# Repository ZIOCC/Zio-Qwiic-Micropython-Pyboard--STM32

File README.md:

# Zio-Qwiic-Micropython-Pyboard--STM32

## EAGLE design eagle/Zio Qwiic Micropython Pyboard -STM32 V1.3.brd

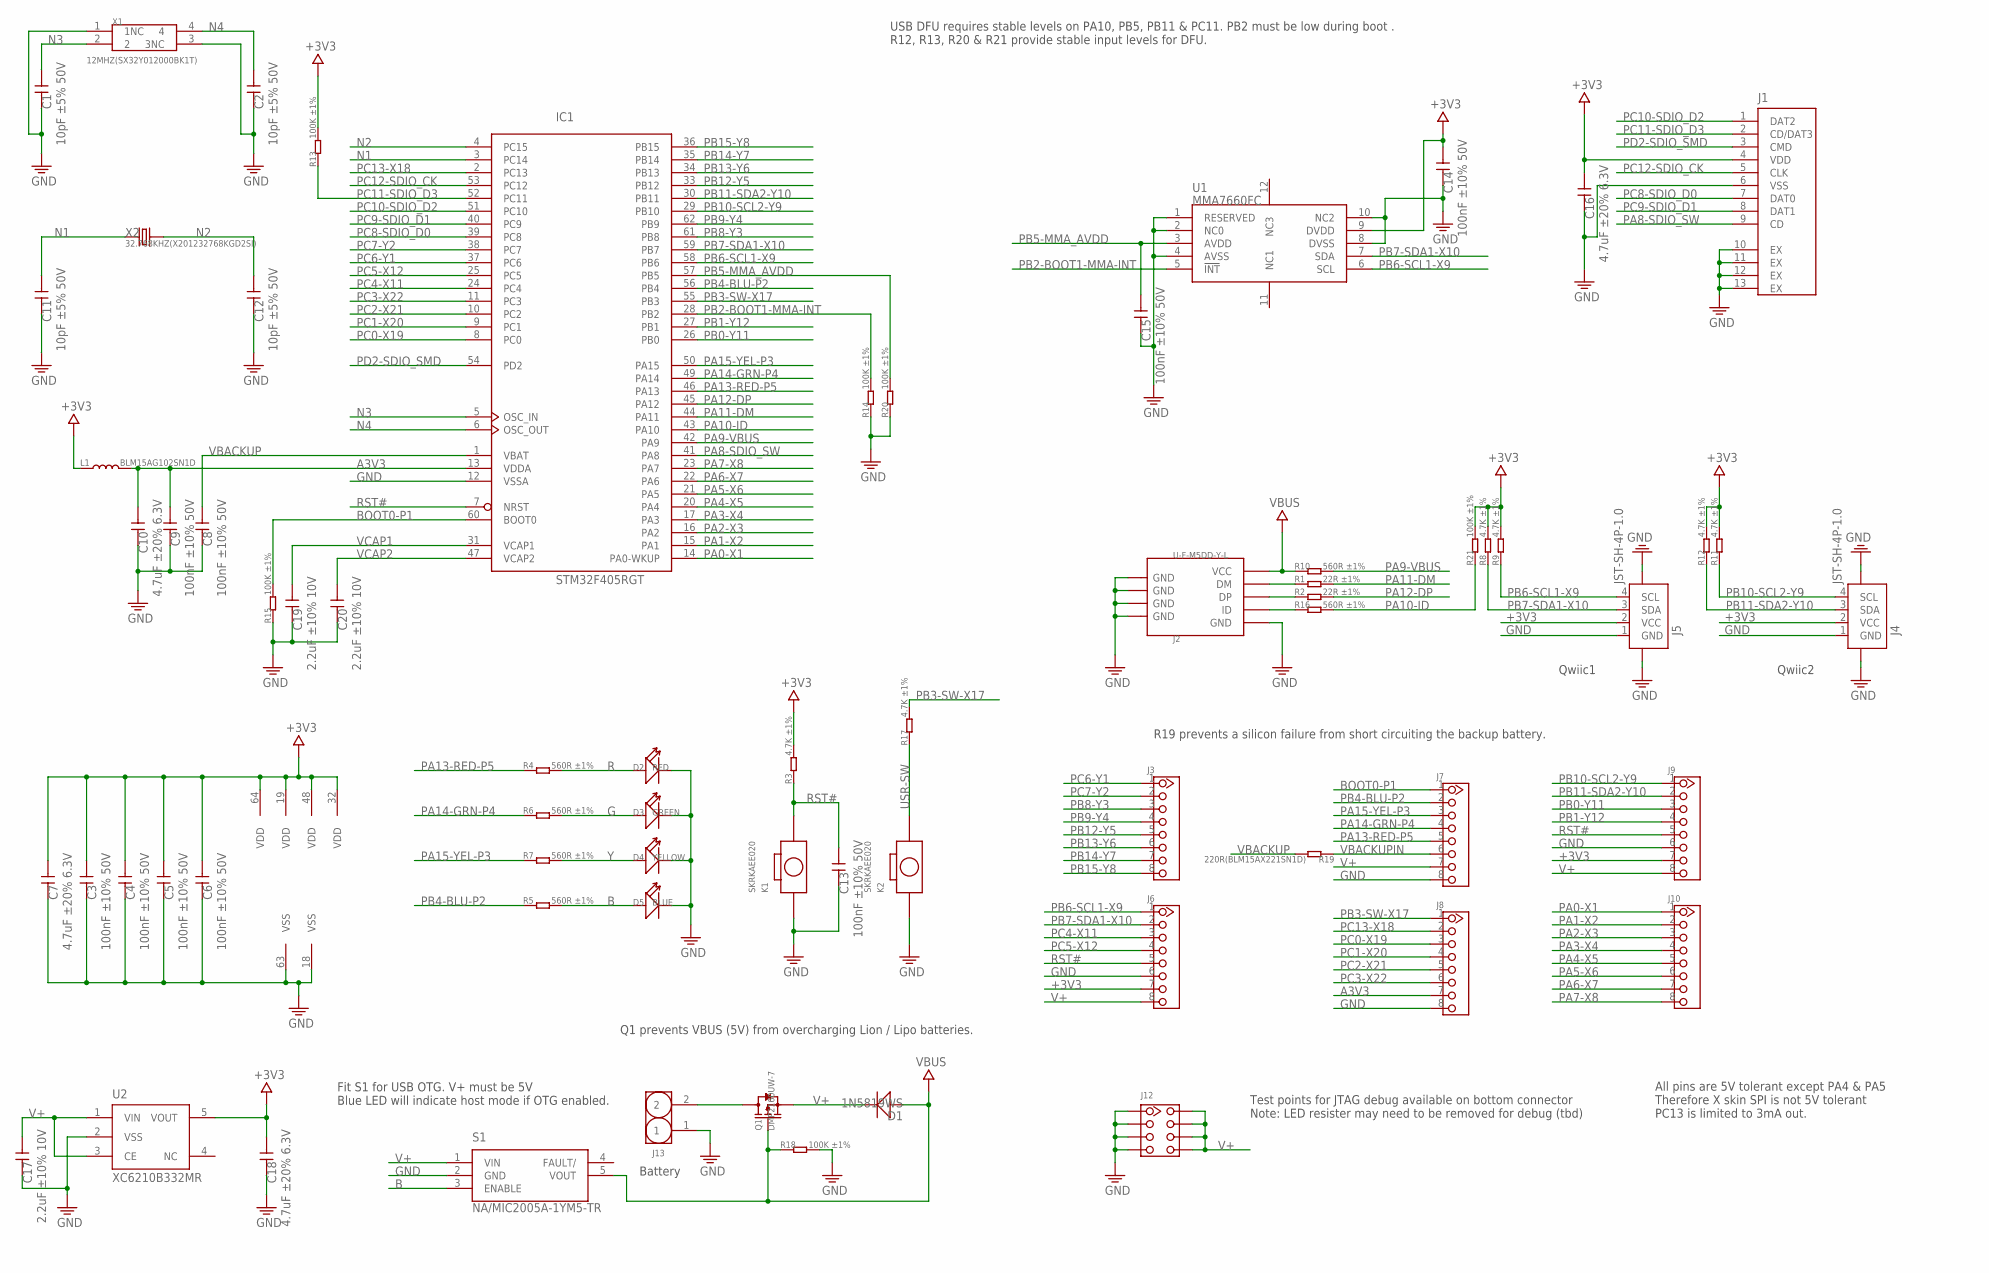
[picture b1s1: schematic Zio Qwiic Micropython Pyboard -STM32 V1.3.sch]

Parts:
C1, C2, C11, C12: 10pF ±5% 50V; C0402
C3, C4, C5, C6, C8, C9, C13, C14, C15: 100nF ±10% 50V; C0402
C7, C10, C16, C18: 4.7uF ±20% 6.3V; C0402
C17, C19, C20: 2.2uF ±10% 10V; C0402
D1: 1N5819WS; SOD323
D2: RED; LED-0603
D3: GREEN; LED-0603
D4: YELLOW; LED-0603
D5: BLUE; LED-0603
IC1: STM32F405RGT; LQFP64
J1: TF_CARD
J2: U-F-M5DD-Y-L; MICRO-SMD
J3, J6, J7, J8, J9, J10: HEADER-8P-NS; 8P-2.54-60/35MIL-NS
J4, J5: JST-SH-4P-1.0; JST-SH-4P
J12: HEADER-2X4P-NS; 2X4P-2.54-NS
J13: HEADER-2P-2.0-90; PH2.0-2P-90
K1, K2: SKRKAEE020
L1: BLM15AG102SN1D; L0402
Q1: DMP2160UW-7; SOT-323
R1, R2: 22R ±1%; R0402
R3, R8, R9, R11, R12, R17: 4.7K ±1%; R0402
R4, R5, R6, R7, R10, R16: 560R ±1%; R0402
R13, R14, R15, R18, R20, R21: 100K ±1%; R0402
R19: 220R(BLM15AX221SN1D); R0402
S1: NA/MIC2005A-1YM5-TR; SOT95P280X130-5N
U1: MMA7660FC; DFN10
U2: XC6210B332MR; SOT23-5
X1: 12MHZ(SX32Y012000BK1T); 4P-SMD-3.2X2.5
X2: 32.768KHZ(X201232768KGD2SI); 2.0X12MM

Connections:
+3V3: C3.2, C4.2, C5.2, C6.2, C7.2, C14.2, C16.2, C18.2, IC1.19 (VDD), IC1.32 (VDD), IC1.48 (VDD), IC1.64 (VDD), J1.4 (VDD), J4.2 (VCC), J5.2 (VCC), J6.7, J9.7, L1.1, R3.2, R8.2, R9.2, R11.2, R12.2, R13.2, R21.2, U1.9 (DVDD), U2.5 (VOUT)
A3V3: C9.2, C10.2, IC1.13 (VDDA), J8.7, L1.2
B: D5.+, R5.2, S1.3 (ENABLE)
BOOT0-P1: IC1.60 (BOOT0), J7.1, R15.2
G: D3.+, R6.2
GND: C1.1, C2.1, C3.1, C4.1, C5.1, C6.1, C7.1, C8.1, C9.1, C10.1, C11.1, C12.1, C13.1, C14.1, C15.1, C16.1, C17.1, C18.1, C19.1, C20.1, D2.-, D3.-, D4.-, D5.-, IC1.12 (VSSA), IC1.18 (VSS), IC1.63 (VSS), J1.6 (VSS), J1.10 (EX), J1.11 (EX), J1.12 (EX), J1.13 (EX), J2.GND, J2.S1 (GND), J2.S1@1 (GND), J2.S1@2 (GND), J2.S2 (GND), J2.S2@1 (GND), J2.S2@2 (GND), J2.S3 (GND), J2.S3@1 (GND), J2.S3@2 (GND), J2.S4 (GND), J2.S4@1 (GND), J2.S4@2 (GND), J2.S5 (GND), J2.S6 (GND), J4.1 (GND), J4.NC1 (5), J4.NC2 (6), J5.1 (GND), J5.NC1 (5), J5.NC2 (6), J6.6, J7.8, J8.8, J9.6, J12.1, J12.2, J12.3, J12.4, J13.1, K1.1, K2.1, R14.1, R15.1, R18.2, R20.1, S1.2 (GND), U1.1 (RESERVED), U1.2 (NC0), U1.4 (AVSS), U1.8 (DVSS), U1.10 (NC2), U2.2 (VSS), X1.1 (1NC), X1.3 (3NC)
N1: C11.2, IC1.3 (PC14), X2.1
N2: C12.2, IC1.4 (PC15), X2.2
N3: C1.2, IC1.5 (OSC_IN), X1.2
N4: C2.2, IC1.6 (OSC_OUT), X1.4
unnamed: J2.D- (DM), R1.1
unnamed: J2.D+ (DP), R2.1
unnamed: J2.ID, R16.1
unnamed: J13.2, Q1.3 (D)
PA0-X1: IC1.14 (PA0-WKUP), J10.1
PA1-X2: IC1.15 (PA1), J10.2
PA2-X3: IC1.16 (PA2), J10.3
PA3-X4: IC1.17 (PA3), J10.4
PA4-X5: IC1.20 (PA4), J10.5
PA5-X6: IC1.21 (PA5), J10.6
PA6-X7: IC1.22 (PA6), J10.7
PA7-X8: IC1.23 (PA7), J10.8
PA8-SDIO_SW: IC1.41 (PA8), J1.9 (CD)
PA9-VBUS: IC1.42 (PA9), R10.2
PA10-ID: IC1.43 (PA10), R16.2, R21.1
PA11-DM: IC1.44 (PA11), R1.2
PA12-DP: IC1.45 (PA12), R2.2
PA13-RED-P5: IC1.46 (PA13), J7.5, R4.1
PA14-GRN-P4: IC1.49 (PA14), J7.4, R6.1
PA15-YEL-P3: IC1.50 (PA15), J7.3, R7.1
PB0-Y11: IC1.26 (PB0), J9.3
PB1-Y12: IC1.27 (PB1), J9.4
PB2-BOOT1-MMA-INT: IC1.28 (PB2), R14.2, U1.5 (!INT)
PB3-SW-X17: IC1.55 (PB3), J8.1, R17.2
PB4-BLU-P2: IC1.56 (PB4), J7.2, R5.1
PB5-MMA_AVDD: C15.2, IC1.57 (PB5), R20.2, U1.3 (AVDD)
PB6-SCL1-X9: IC1.58 (PB6), J5.4 (SCL), J6.1, R9.1, U1.6 (SCL)
PB7-SDA1-X10: IC1.59 (PB7), J5.3 (SDA), J6.2, R8.1, U1.7 (SDA)
PB8-Y3: IC1.61 (PB8), J3.3
PB9-Y4: IC1.62 (PB9), J3.4
PB10-SCL2-Y9: IC1.29 (PB10), J4.4 (SCL), J9.1, R11.1
PB11-SDA2-Y10: IC1.30 (PB11), J4.3 (SDA), J9.2, R12.1
PB12-Y5: IC1.33 (PB12), J3.5
PB13-Y6: IC1.34 (PB13), J3.6
PB14-Y7: IC1.35 (PB14), J3.7
PB15-Y8: IC1.36 (PB15), J3.8
PC0-X19: IC1.8 (PC0), J8.3
PC1-X20: IC1.9 (PC1), J8.4
PC2-X21: IC1.10 (PC2), J8.5
PC3-X22: IC1.11 (PC3), J8.6
PC4-X11: IC1.24 (PC4), J6.3
PC5-X12: IC1.25 (PC5), J6.4
PC6-Y1: IC1.37 (PC6), J3.1
PC7-Y2: IC1.38 (PC7), J3.2
PC8-SDIO_D0: IC1.39 (PC8), J1.7 (DAT0)
PC9-SDIO_D1: IC1.40 (PC9), J1.8 (DAT1)
PC10-SDIO_D2: IC1.51 (PC10), J1.1 (DAT2)
PC11-SDIO_D3: IC1.52 (PC11), J1.2 (CD/DAT3), R13.1
PC12-SDIO_CK: IC1.53 (PC12), J1.5 (CLK)
PC13-X18: IC1.2 (PC13), J8.2
PD2-SDIO_SMD: IC1.54 (PD2), J1.3 (CMD)
R: D2.+, R4.2
RST#: C13.2, IC1.7 (NRST), J6.5, J9.5, K1.2, R3.1
USR-SW: K2.2, R17.1
V+: C17.2, D1.-, J6.8, J7.7, J9.8, J12.5, J12.6, J12.7, J12.8, Q1.2 (S), S1.1 (VIN), U2.1 (VIN), U2.3 (CE)
VBACKUP: C8.2, IC1.1 (VBAT), R19.2
VBACKUPIN: J7.6, R19.1
VBUS: D1.+, J2.VBUS (VCC), Q1.1 (G), R10.1, R18.1, S1.5 (VOUT)
VCAP1: C19.2, IC1.31 (VCAP1)
VCAP2: C20.2, IC1.47 (VCAP2)
Y: D4.+, R7.2

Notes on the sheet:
Qwiic1
Qwiic2
Battery
USB DFU requires stable levels on PA10, PB5, PB11 & PC11. PB2 must be low during boot . R12, R13, R20 & R21 provide stable input levels for DFU.
Q1 prevents VBUS (5V) from overcharging Lion / Lipo batteries.
Fit S1 for USB OTG. V+ must be 5V Blue LED will indicate host mode if OTG enabled.
Test points for JTAG debug available on bottom connector Note: LED resister may need to be removed for debug (tbd)
R19 prevents a silicon failure from short circuiting the backup battery.
All pins are 5V tolerant except PA4 & PA5 Therefore X skin SPI is not 5V tolerant PC13 is limited to 3mA out.

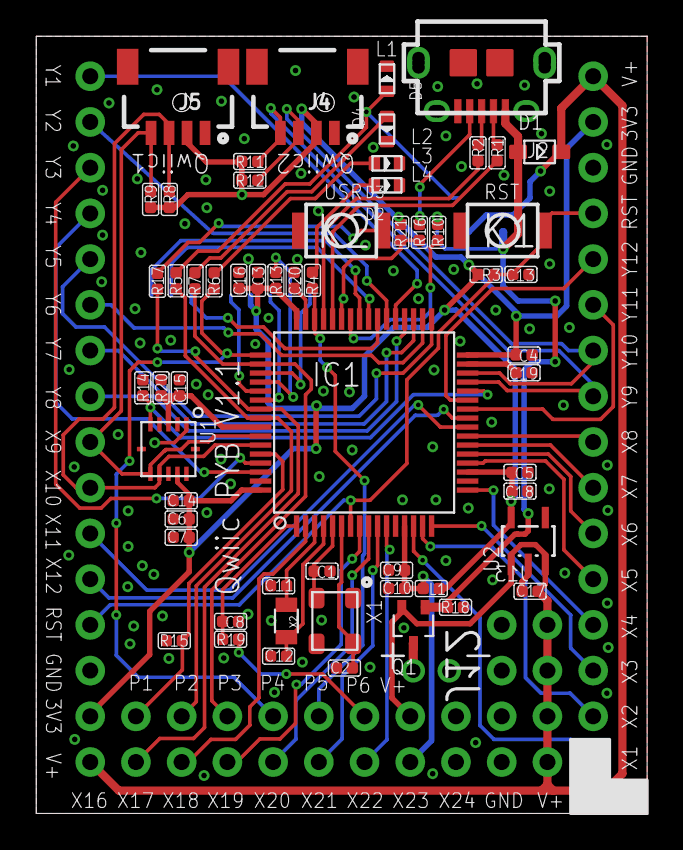
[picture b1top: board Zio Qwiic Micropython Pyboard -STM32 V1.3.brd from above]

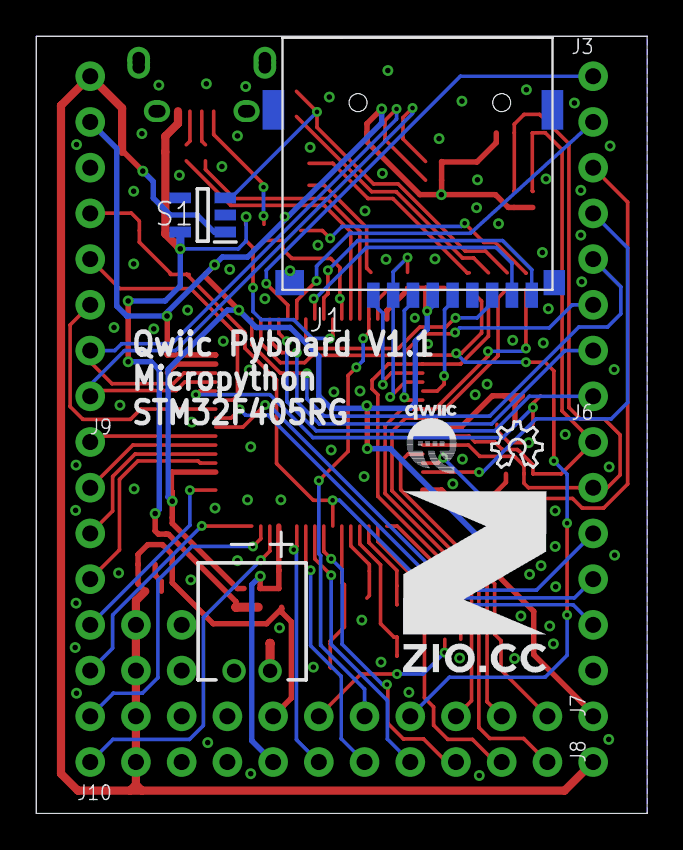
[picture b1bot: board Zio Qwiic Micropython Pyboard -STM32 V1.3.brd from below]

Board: 2 copper layers, 33.9 x 43.2 mm, 71 parts (13 on the bottom side), 71 nets.

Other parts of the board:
U$12: 10MM
U$13: QWIIC-LOGO-SMALL
U$14: OSHW_6X100_NOTEXT

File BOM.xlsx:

| BOM/PCBA quantity:
 | Project Name:
# | Part ID/Reference | Manufacturer | Part Number | Description | Value | Package | THT | Pins/Pads Qty | Source/Link/Datasheet/Note | Quantity/per BOM | NOTE
1 | C1, C2, C11, C12 |  |  |  | 10pF ±5% 50V | C0402 |  |  |  | 4
2 | C3, C4, C5, C6, C8, C9, C13, C14, C15 |  |  |  | 100nF ±10% 50V | C0402 |  |  |  | 9
3 | C7, C10, C16, C18 |  |  |  | 4.7uF ±20% 6.3V | C0402 |  |  |  | 4
4 | C17, C19, C20 |  |  |  | 2.2uF ±10% 10V | C0402 |  |  |  | 3
5 | D1 |  | 1N5819WS |  | 1N5819WS | SOD323 |  |  |  | 1
6 | D2 |  |  |  | RED | LED-0603 |  |  |  | 1
7 | D3 |  |  |  | GREEN | LED-0603 |  |  |  | 1
8 | D4 |  |  |  | YELLOW | LED-0603 |  |  |  | 1
9 | D5 |  |  |  | BLUE | LED-0603 |  |  |  | 1
10 | IC1 |  | STM32F405RGT |  | STM32F405RGT | LQFP64 |  |  |  | 1
11 | J1 |  | 带自弹TF卡座 |  | TF_CARD | TF_CARD |  |  |  | 1
12 | J2 |  | U-F-M5DD-Y-L |  | U-F-M5DD-Y-L | MICRO-SMD |  |  |  | 1
13 | J3, J6, J7, J8, J9, J10 |  | NA |  | NA | 8P-2.54-60/35MIL-NS |  |  |  | 6
14 | J4, J5 |  |  |  | JST-SH-4P-1.0 | JST-SH-4P |  |  |  | 2
15 | J12 |  | NA |  | NA | 2X4P-2.54-NS |  |  |  | 1
16 | J13 |  | NA |  | NA | PH2.0-2P-90 |  |  |  | 1
17 | K1, K2 |  | SKRKAEE020 |  | SKRKAEE020 | SKRKAEE020 |  |  |  | 2
18 | L1 |  | BLM15AG102SN1D |  | BLM15AG102SN1D | L0402 |  |  |  | 1
19 | Q1 |  | DMP2160UW-7 |  | DMP2160UW-7 | SOT-323 |  |  |  | 1
20 | R1, R2 |  |  |  | 22R ±1% | R0402 |  |  |  | 2
21 | R3, R8, R9, R11, R12, R17 |  |  |  | 4.7K ±1% | R0402 |  |  |  | 6
22 | R4, R5, R6, R7, R10, R16 |  |  |  | 560R ±1% | R0402 |  |  |  | 6
23 | R13, R14, R15, R18, R20, R21 |  |  |  | 100K ±1% | R0402 |  |  |  | 6
24 | R19 |  | BLM15AX221SN1D |  | 220R ±1% | R0402 |  |  |  | 1
25 | S1 |  | NA |  | NA/MIC2005A-1YM5-TR | SOT95P280X130-5N |  |  |  | 1
26 | U1 |  | MMA7660FC |  | MMA7660FC | DFN10 |  |  |  | 1
27 | U2 |  | XC6210B332MR |  | XC6210B332MR | SOT23-5 |  |  |  | 1
28 | X1 |  | SX32Y012000BK1T |  | 12MHZ(SX32Y012000BK1T) | 4P-SMD-3.2X2.5 |  |  |  | 1
29 | X2 |  | X201232768KGD2SI |  | 32.768KHZ(X201232768KGD2SI) | 2.0X12MM |  |  |  | 1
